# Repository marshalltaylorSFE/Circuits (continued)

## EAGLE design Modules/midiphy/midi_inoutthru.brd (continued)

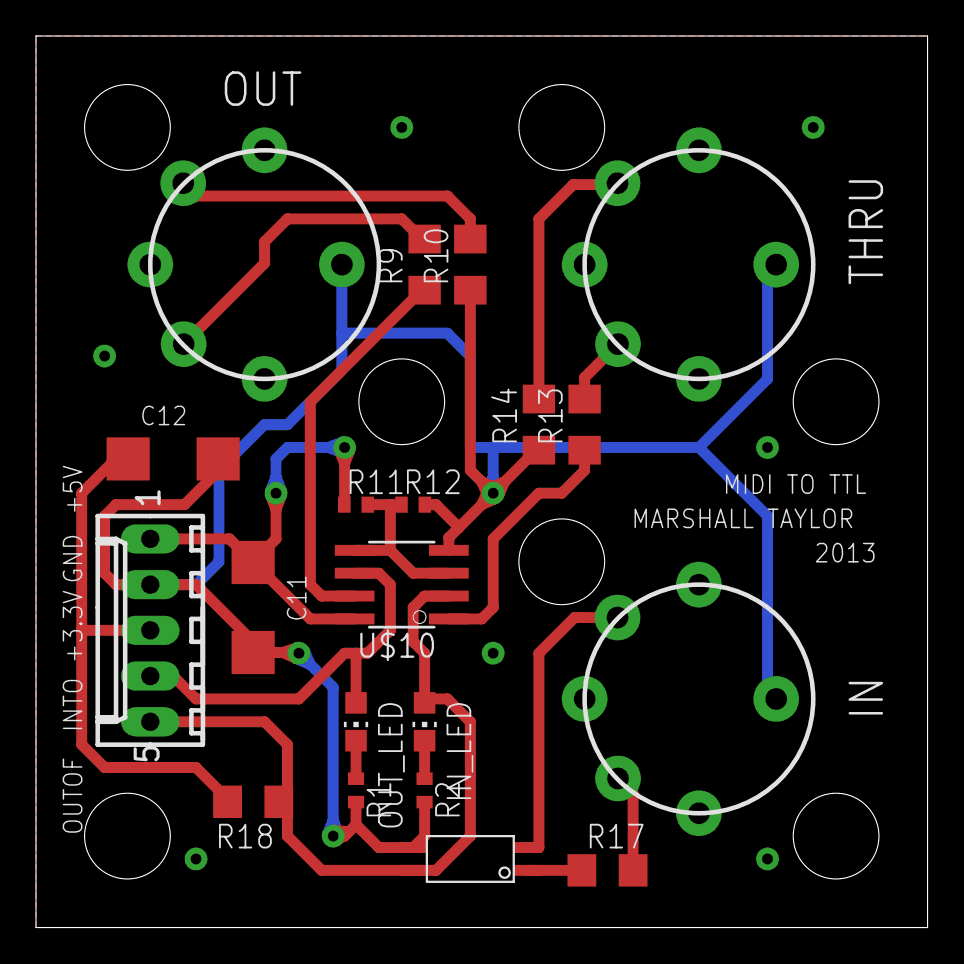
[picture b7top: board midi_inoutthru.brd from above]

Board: 2 copper layers, 49.5 x 49.5 mm, 20 parts (0 on the bottom side), 17 nets.

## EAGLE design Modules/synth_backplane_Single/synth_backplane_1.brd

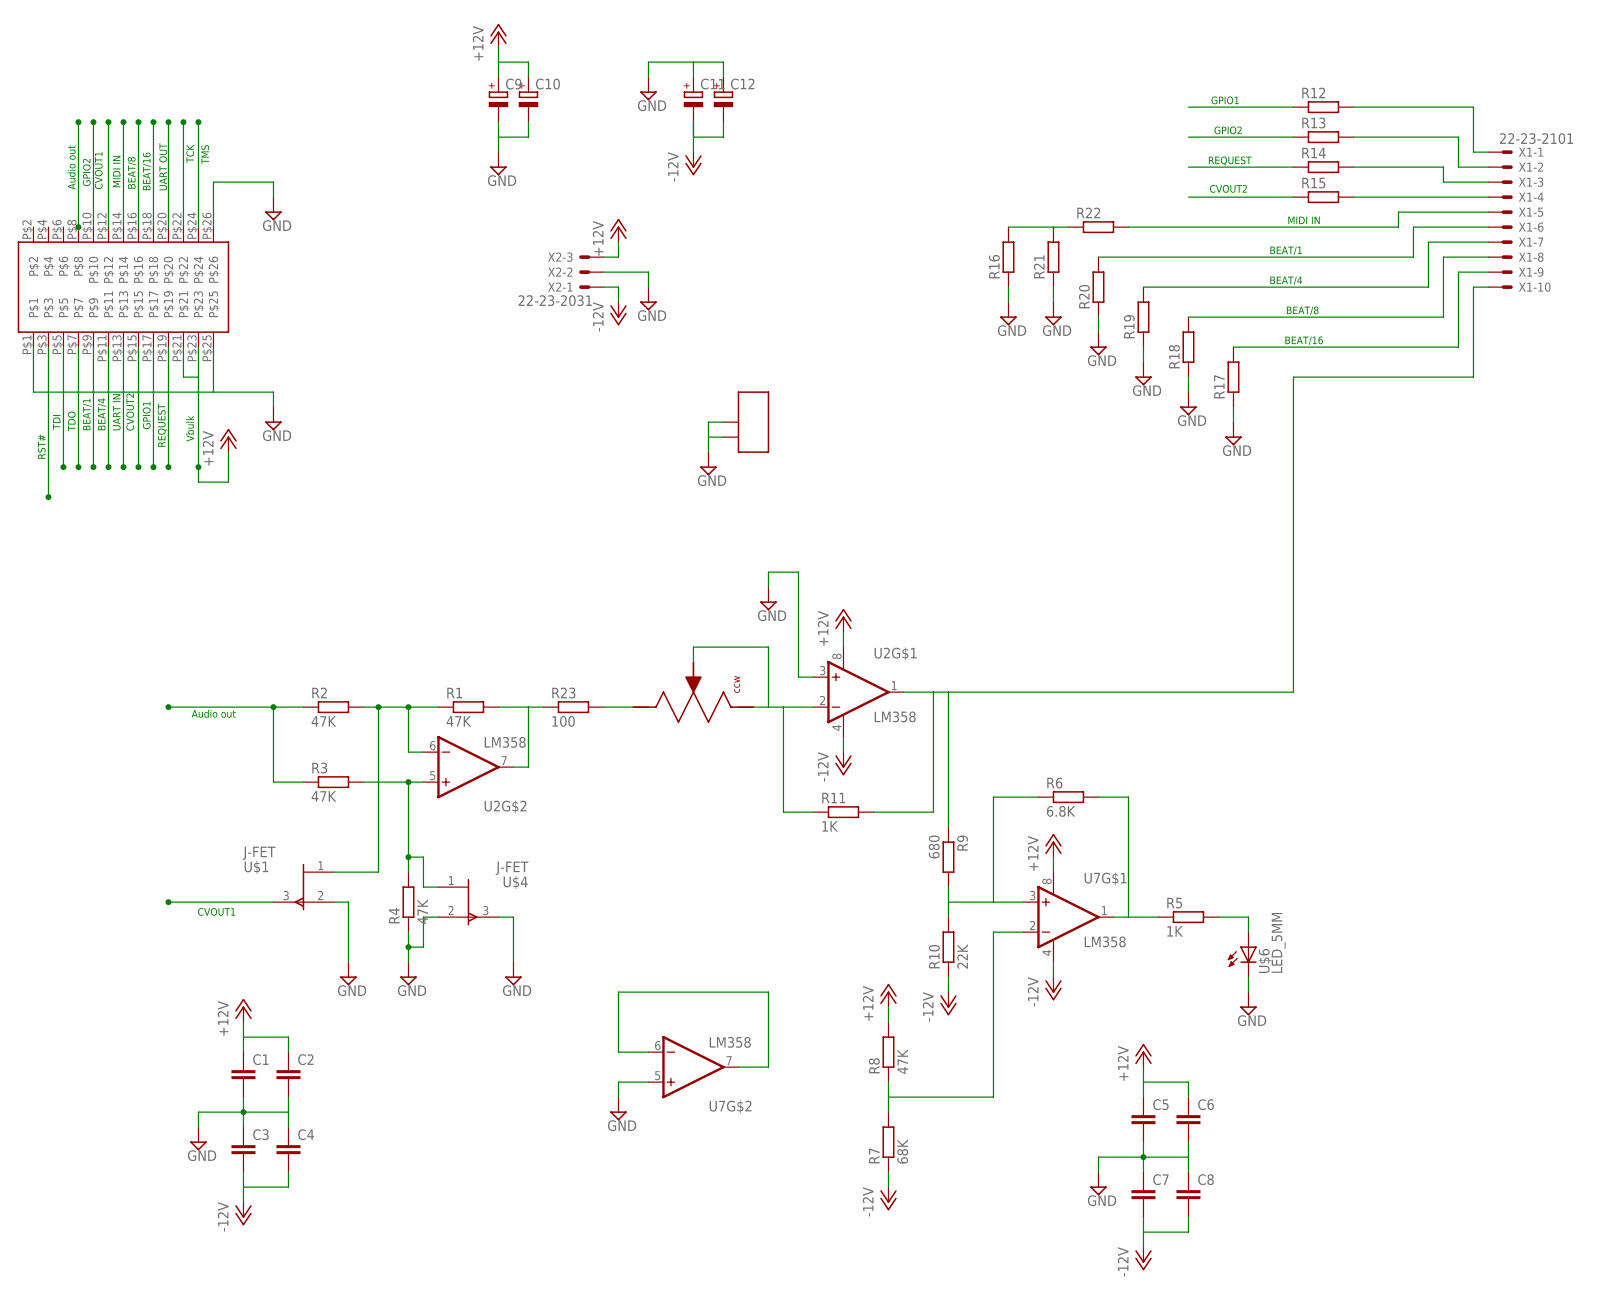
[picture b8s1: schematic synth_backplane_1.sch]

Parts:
C1, C2, C3, C4, C5, C6, C7, C8: C-EUC0603K; C0603K
C9, C10, C11, C12: CPOL-EUSMCE; SMC_E
R1, R2, R3, R4, R8: 47K; R0603
R5, R11: 1K; R0603
R6: 6.8K; R0603
R7: 68K; R0603
R9: 680; R0603
R10: 22K; R0603
R12, R13, R14, R15, R16, R17, R18, R19, R20, R21, R22: R-EU_R0603; R0603
R23: 100; R0603
U2, U7: LM358; SO08
U$1, U$4: J-FET; SOT_23
U$3: TE_EDGECON_26_SOCKET; TE_EDGE_26_SOCKET
U$5: POT_MODEL_P090
U$6: LED_5MM; LED5MM
X1: 22-23-2101
X2: 22-23-2031

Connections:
+12V: C1.1, C2.1, C5.1, C6.1, C9.+, C10.+, R8.2, U2.8 (V+), U7.8 (V+), U$3.P$21, U$3.P$23, X2.3
-12V: C3.2, C4.2, C7.2, C8.2, C11.-, C12.-, R7.1, R10.1, U2.4 (V-), U7.4 (V-), X2.1
AUD_OUT: R2.1, R3.1, U$3.P$8
BEAT/1: R20.2, U$3.P$9, X1.6
BEAT/4: R19.2, U$3.P$11, X1.7
BEAT/8: R18.2, U$3.P$16, X1.8
BEAT/16: R17.2, U$3.P$18, X1.9
CVOUT1: U$1.3 (G), U$3.P$12
CVOUT2: R15.1, U$3.P$15
GND: C1.2, C2.2, C3.1, C4.1, C5.2, C6.2, C7.1, C8.1, C9.-, C10.-, C11.+, C12.+, R4.1, R16.1, R17.1, R18.1, R19.1, R20.1, R21.1, U2.3 (+IN), U7.5 (+IN), U$1.2 (S), U$3.P$1, U$3.P$25, U$3.P$26, U$4.2 (S), U$4.3 (G), U$5.P$4, U$5.P$5, U$6.K (C), X2.2
GPIO1: R12.1, U$3.P$17
GPIO2: R13.1, U$3.P$10
unnamed: R23.2, U$5.P$1 (R2)
unnamed: R5.1, R6.2, U7.1 (OUT)
unnamed: R5.2, U$6.A
unnamed: R6.1, R9.2, R10.2, U7.3 (+IN)
unnamed: R7.2, R8.1, U7.2 (-IN)
unnamed: U7.6 (-IN), U7.7 (OUT)
unnamed: R11.1, U2.2 (-IN), U$5.P$2 (RVAR), U$5.P$3 (CCW)
unnamed: R12.2, X1.1
unnamed: R13.2, X1.2
unnamed: R14.2, X1.3
unnamed: R15.2, X1.4
unnamed: R9.1, R11.2, U2.1 (OUT), X1.10
R10: R1.2, R23.1, U2.7 (OUT)
REQUEST: R14.1, U$3.P$19
RST#: U$3.P$3
TCK: U$3.P$22
TDI: U$3.P$5
TDO: U$3.P$7
TMS: U$3.P$24
UCA0RXD: R16.2, R21.2, R22.1, U$3.P$14
UCA0RXD_BUS: R22.2, X1.5
UCA1RXD1: U$3.P$13
UCA1TXD: U$3.P$20
VN: R1.1, R2.2, U2.6 (-IN), U$1.1 (D)
VP: R3.2, R4.2, U2.5 (+IN), U$4.1 (D)

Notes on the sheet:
TDO
TDI
TMS
TCK
RST#
MIDI IN
UART IN
UART OUT
Vbulk
Audio out
CVOUT1
CVOUT2
BEAT/1
BEAT/4
BEAT/8
BEAT/16
GPIO1
GPIO2
REQUEST

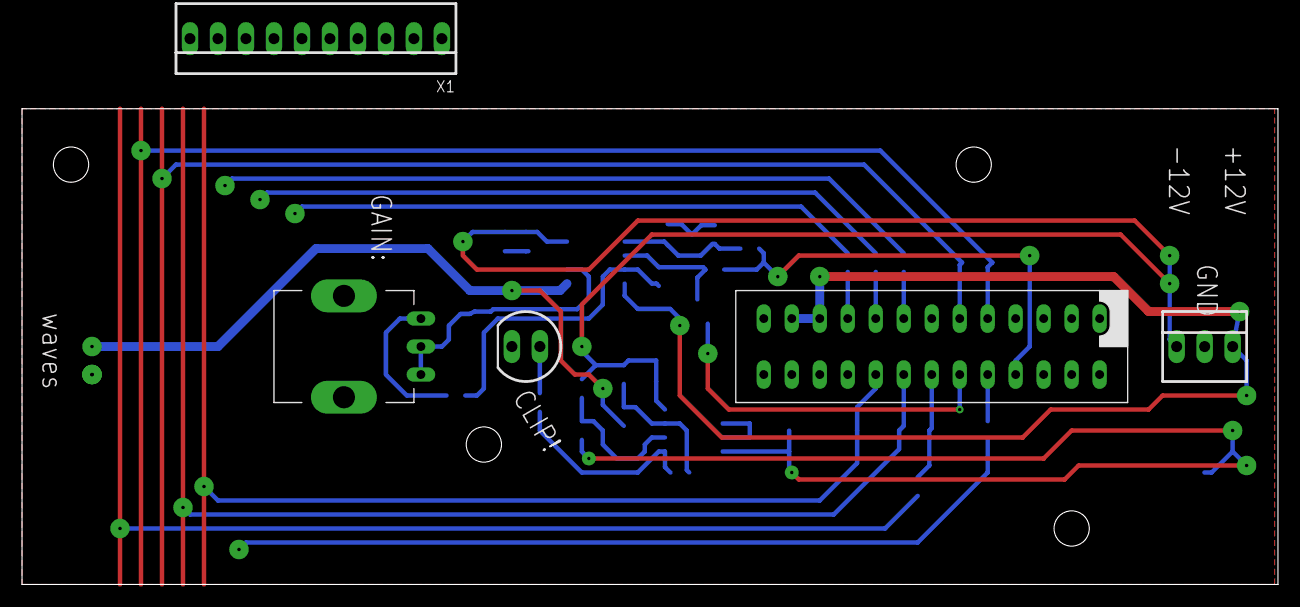
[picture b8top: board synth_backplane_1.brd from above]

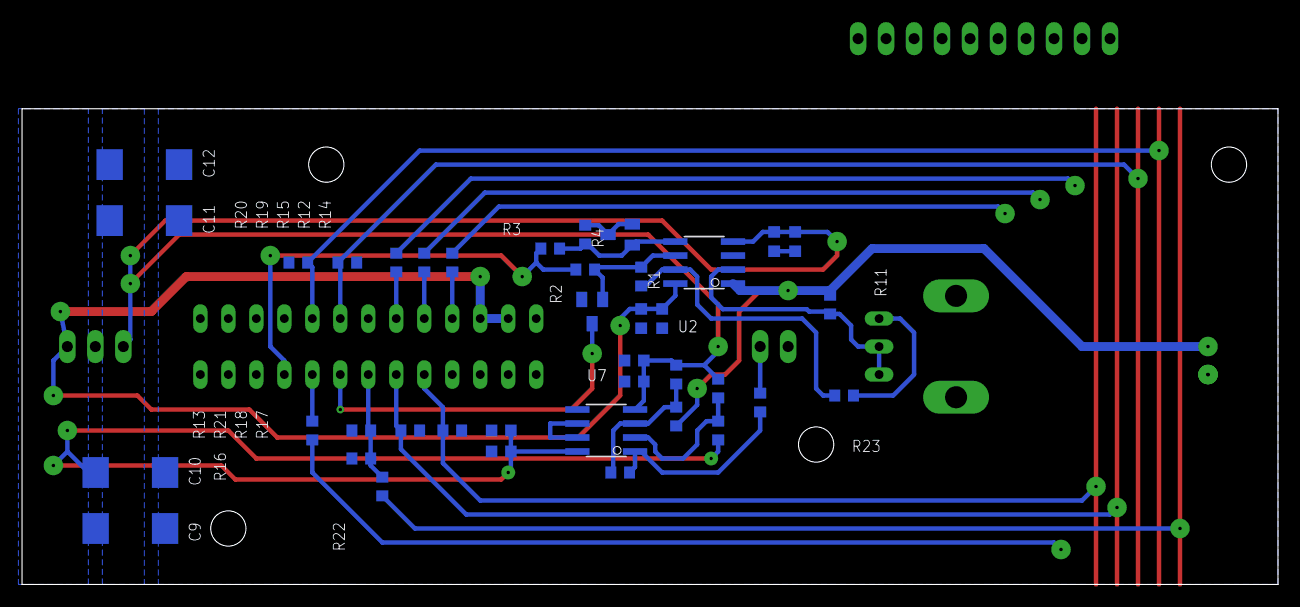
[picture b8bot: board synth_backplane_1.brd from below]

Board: 2 copper layers, 114.0 x 43.2 mm, 44 parts (39 on the bottom side), 30 nets.
